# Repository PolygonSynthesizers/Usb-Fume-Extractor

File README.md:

# Usb-Fume-Extractor
This is a USB powered (5v) PWM Computer Fan Controller

Please read until the end!

This fume extractor is made with a 120 mm PWM (4pin) 12V PC Fan. 
You can use any 12V PC Fan as long as the power consomption doesn't exceed 500mA over 12V.
It has to be a 12V fan as the power supply is converting 5V USB to 12V. 24V Fans won't work.
I personally use a Noctua NF-F12 industrialPPC-3000 PWM and it can blow air 
along 6 meter of 80mm aluminium duct even at half speed.

You can control the speed of rotation via the potentiometer around 10 to 90% of the fan full speed.
It works with a 556 chip (which is two 555 timers in DIP 14 pins package) which produce a 5V square pulse
with pulse width modulation (it's how fan speed is controlled on a computer).

You can't power this circuit with a computer USB port. It doesn't have enough power. You have to power it with
a USB Power Supply like a Phone Charger for example. It has to be rated for 1 amp over 5V at a minimum. 
Connect the charger to the board via a USB A to USB A cable or a USB A to USB B cable (Printer cable). 
About the length : the shorter is the better.  

Some references :

* U1 is a NE556 in DIP14 package
* The inductor is a 10 uH Fastron 242408 FPS
* U2 is a LM2731 XMF in SOT-23 package
* R1 and R2 are 0805
* CF1 is 0805
* C1 is 1210
* C2 is 1812
* D1 is .5 amps Schottky Rectifier in SOD-123 package
* All through hole resistors are 1/4W
* All through hole capacitors are 5mm pitch film capacitors
* Except for C7 which is a 2mm pitch aluminium electrolytic.
* RV1 is a Alps Alpine RK09K113 10k Linear (Log can also work but control over speed will not be linear).
* SW1 is a 3 pin SPDT switch with 4.7mm pitch between pins. I has to be rated for 1A at least.

For values you can check the BOM under the bom folder. Values are also on the schematics.
All SMDs can be handsoldered. Start with the LM2731XMF.

This project has been made with KiCad 7.01. You may have to install the latest version of KiCad
for this project to work.
I have made some custom footprints for the switch, the inductor and the film capacitors.
They can be found under the Custom Footprints folder.

Gerbers are available for JLCPCB production under the Gerbers folder. 
Please make your own gerbers if you want to use an other PCB Manufacturer.

I'm providing some 3D files that can be modified on Solidworks. STL Files are also provided so you can print
them on your 3D printer. The rear body of the Fan has been made for 80mm duct. 
Feel free to modifiy it at your own conveniance.
It uses standard M4 screws for the body and M3 screws for the PCB holder.
Files can be found under the 3D Files folder. I will provide some 3d files for the base 
and the PCB front cover later. 
Don't be scared to make your own.

PLEASE DON'T TURN ON THE FAN WITHOUT THE 3D PRINTED FRONT AND REAR BODY PART ATTACHED TO IT !
IT CAN CUT OUT YOUR FINGERS VERY EASILY !
I WON'T TAKE ANY RESPONSABILITY FOR ANY DAMAGE, MATERIAL OR PHYSICAL. YOU HAVE BEEN WARNED !

ENJOY !

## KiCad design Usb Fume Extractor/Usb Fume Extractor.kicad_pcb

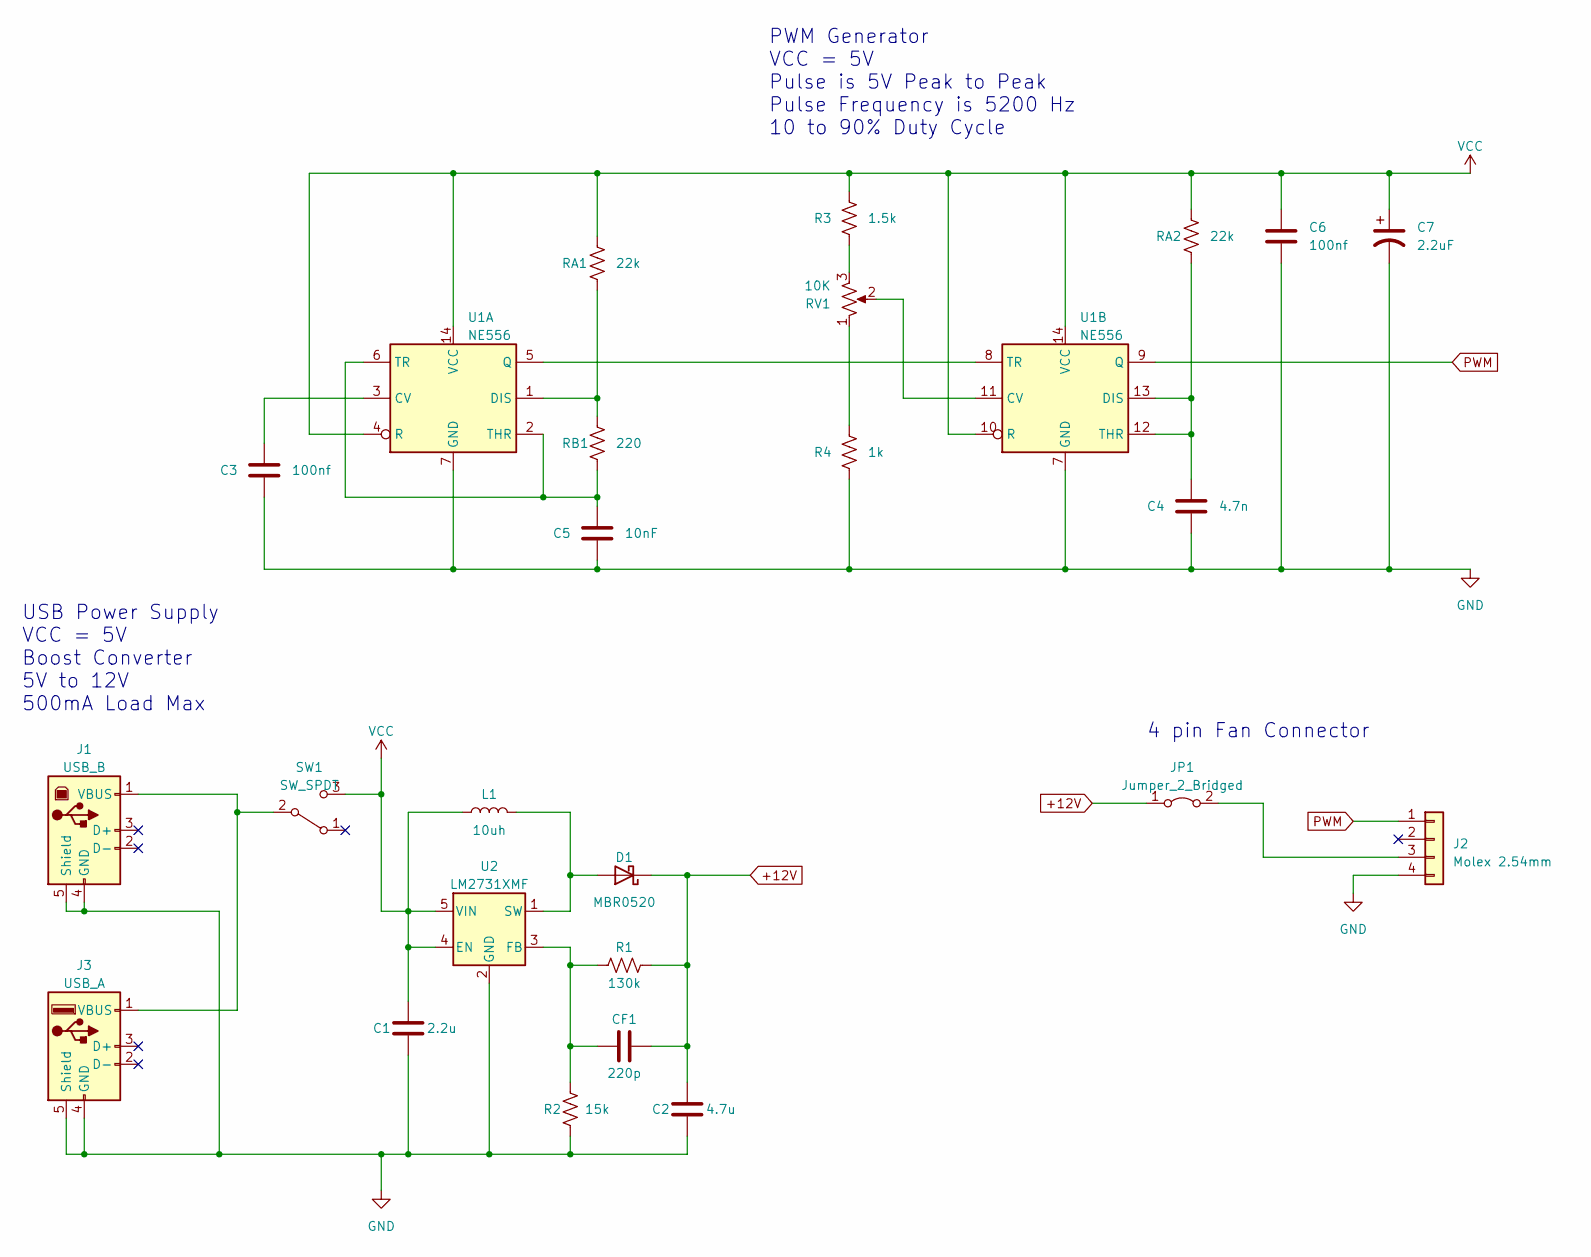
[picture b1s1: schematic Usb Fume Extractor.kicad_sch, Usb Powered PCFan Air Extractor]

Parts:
C1: 2.2u; C_1210_3225Metric_Pad1.33x2.70mm_HandSolder
C2: 4.7u; C_1812_4532Metric_Pad1.57x3.40mm_HandSolder
C3, C6: 100nf; C_Rect_L7.2mm_W2.5mm_P5.00mm_FKS2_FKP2_MKS2_MKP2
C4: 4.7n; C_Rect_L7.2mm_W4.5mm_P5.00mm_FKS2_FKP2_MKS2_MKP2
C5: 10nF; C_Rect_L7.2mm_W6.5mm_P5.00mm_FKS2_FKP2_MKS2_MKP2
C7: 2.2uF; CP_Radial_D5.0mm_P2.00mm
CF1: 220p; C_0805_2012Metric_Pad1.18x1.45mm_HandSolder
D1: MBR0520; D_SOD-123_Handsoldering
J1: USB_B; USB_B_OST_USB-B1HSxx_Horizontal
J2: Molex 2.54mm; Molex_KK-254_AE-6410-04A_1x04_P2.54mm_Vertical
J3: USB_A; USB_A_Wuerth_614004134726_Horizontal
JP1: Jumper_2_Bridged; R_Axial_DIN0309_L9.0mm_D3.2mm_P12.70mm_Horizontal
L1: 10uh; L_Fastron_242408_FPS_Handsoldering
R1: 130k; R_0805_2012Metric_Pad1.20x1.40mm_HandSolder
R2: 15k; R_0805_2012Metric_Pad1.20x1.40mm_HandSolder
R3: 1.5k; R_Axial_DIN0207_L6.3mm_D2.5mm_P10.16mm_Horizontal
R4: 1k; R_Axial_DIN0207_L6.3mm_D2.5mm_P10.16mm_Horizontal
RA1, RA2: 22k; R_Axial_DIN0207_L6.3mm_D2.5mm_P10.16mm_Horizontal
RB1: 220; R_Axial_DIN0207_L6.3mm_D2.5mm_P10.16mm_Horizontal
RV1: 10K; Potentiometer_Alps_RK09K_Single_Vertical
SW1: SW_SPDT; SW_DIP_SPDT_P4.7
U1: NE556; DIP-14_W7.62mm_Socket_LongPads
U2: LM2731XMF; SOT-23-5_HandSoldering

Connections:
+12V: C2.1, CF1.2, D1.1 (K), JP1.1 (A), R1.2
GND: C1.2, C2.2, C3.2, C4.2, C5.2, C6.2, C7.2, J1.4 (GND), J1.5 (Shield), J2.4, J3.4 (GND), J3.5 (Shield), R2.1, R4.2, U1.7 (GND), U2.2 (GND)
unnamed: D1.2 (A), L1.2, U2.1 (SW)
unnamed: J1.1 (VBUS), J3.1 (VBUS), SW1.2 (B)
unnamed: J2.3, JP1.2 (B)
unnamed: R3.2, RV1.3
unnamed: R4.1, RV1.1
unnamed: C3.1, U1.3 (CV)
unnamed: RA1.2, RB1.1, U1.1 (DIS)
unnamed: U1.5 (Q), U1.8 (TR)
unnamed: C5.1, RB1.2, U1.2 (THR), U1.6 (TR)
unnamed: RV1.2, U1.11 (CV)
unnamed: C4.1, RA2.2, U1.12 (THR), U1.13 (DIS)
unnamed: CF1.1, R1.1, R2.2, U2.3 (FB)
PWM: J2.1, U1.9 (Q)
VCC: C1.1, C6.1, C7.1, L1.1, R3.1, RA1.1, RA2.1, SW1.3 (C), U1.4 (R), U1.10 (R), U1.14 (VCC), U2.4 (EN), U2.5 (VIN)

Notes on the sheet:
USB Power Supply VCC = 5V Boost Converter 5V to 12V 500mA Load Max
PWM Generator VCC = 5V Pulse is 5V Peak to Peak Pulse Frequency is 5200 Hz 10 to 90% Duty Cycle
4 pin Fan Connector

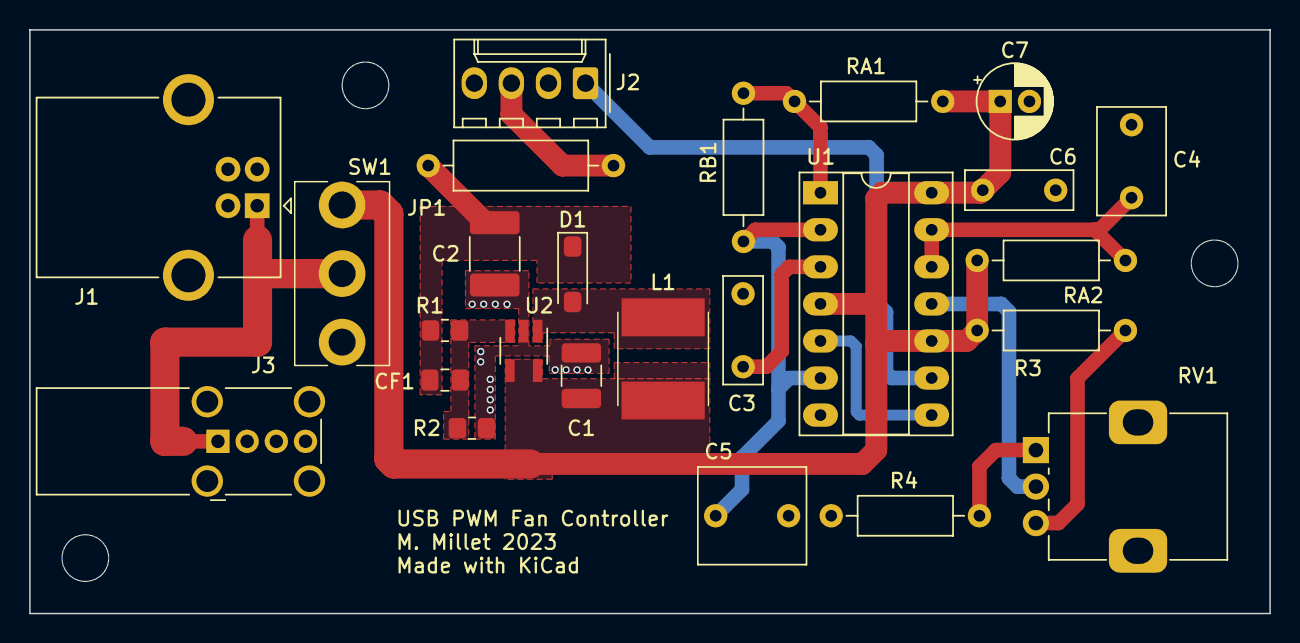
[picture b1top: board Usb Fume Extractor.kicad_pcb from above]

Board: 2 copper layers, 85.0 x 40.0 mm, 25 parts (0 on the bottom side), 16 nets.
